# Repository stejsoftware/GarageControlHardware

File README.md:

# GarageControlHardwarae
Hardware design of Garage Controler

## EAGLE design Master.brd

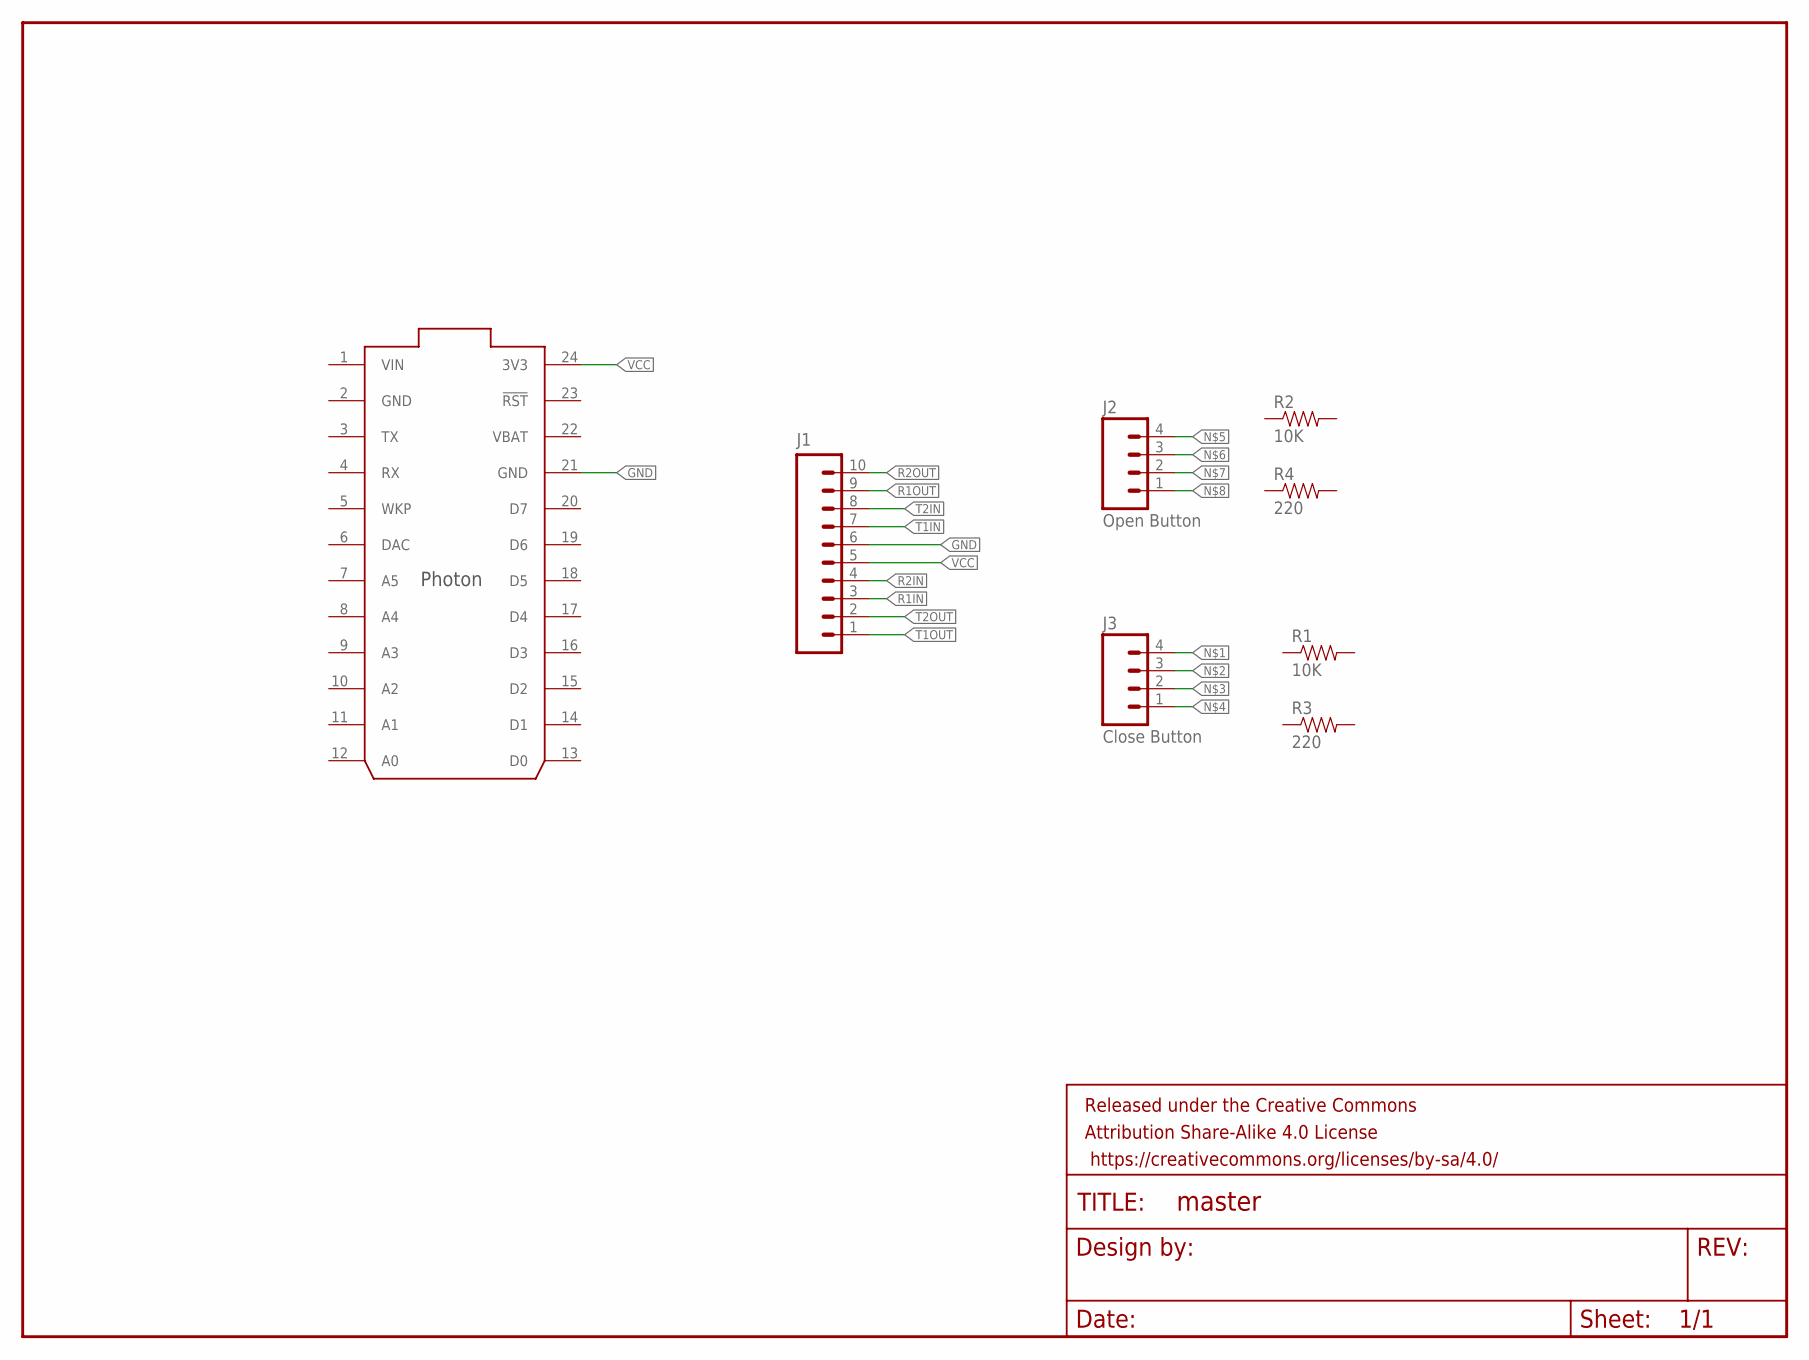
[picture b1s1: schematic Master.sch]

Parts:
FRAME1: FRAME-LETTERNO_PACKAGE; DUMMY
J1: M10SILK_FEMALE_PTH; 1X10
J2: Open Button; 1X04
J3: Close Button; 1X04
R1, R2: 10K; AXIAL-0.4
R3, R4: 220; AXIAL-0.4
U$1: PHOTON_WITH_HEADERS; PHOTON

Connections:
GND: J1.6, U$1.2 (GND), U$1.21 (GND)
R1IN: J1.3
R1OUT: J1.9
R2IN: J1.4
R2OUT: J1.10
T1IN: J1.7
T1OUT: J1.1
T2IN: J1.8
T2OUT: J1.2
VBAT: U$1.22 (VBAT)
VCC: J1.5, U$1.24 (3V3)
VIN: U$1.1 (VIN)

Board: 2 copper layers, 9 parts (0 on the bottom side), 2 nets, no tracks yet.

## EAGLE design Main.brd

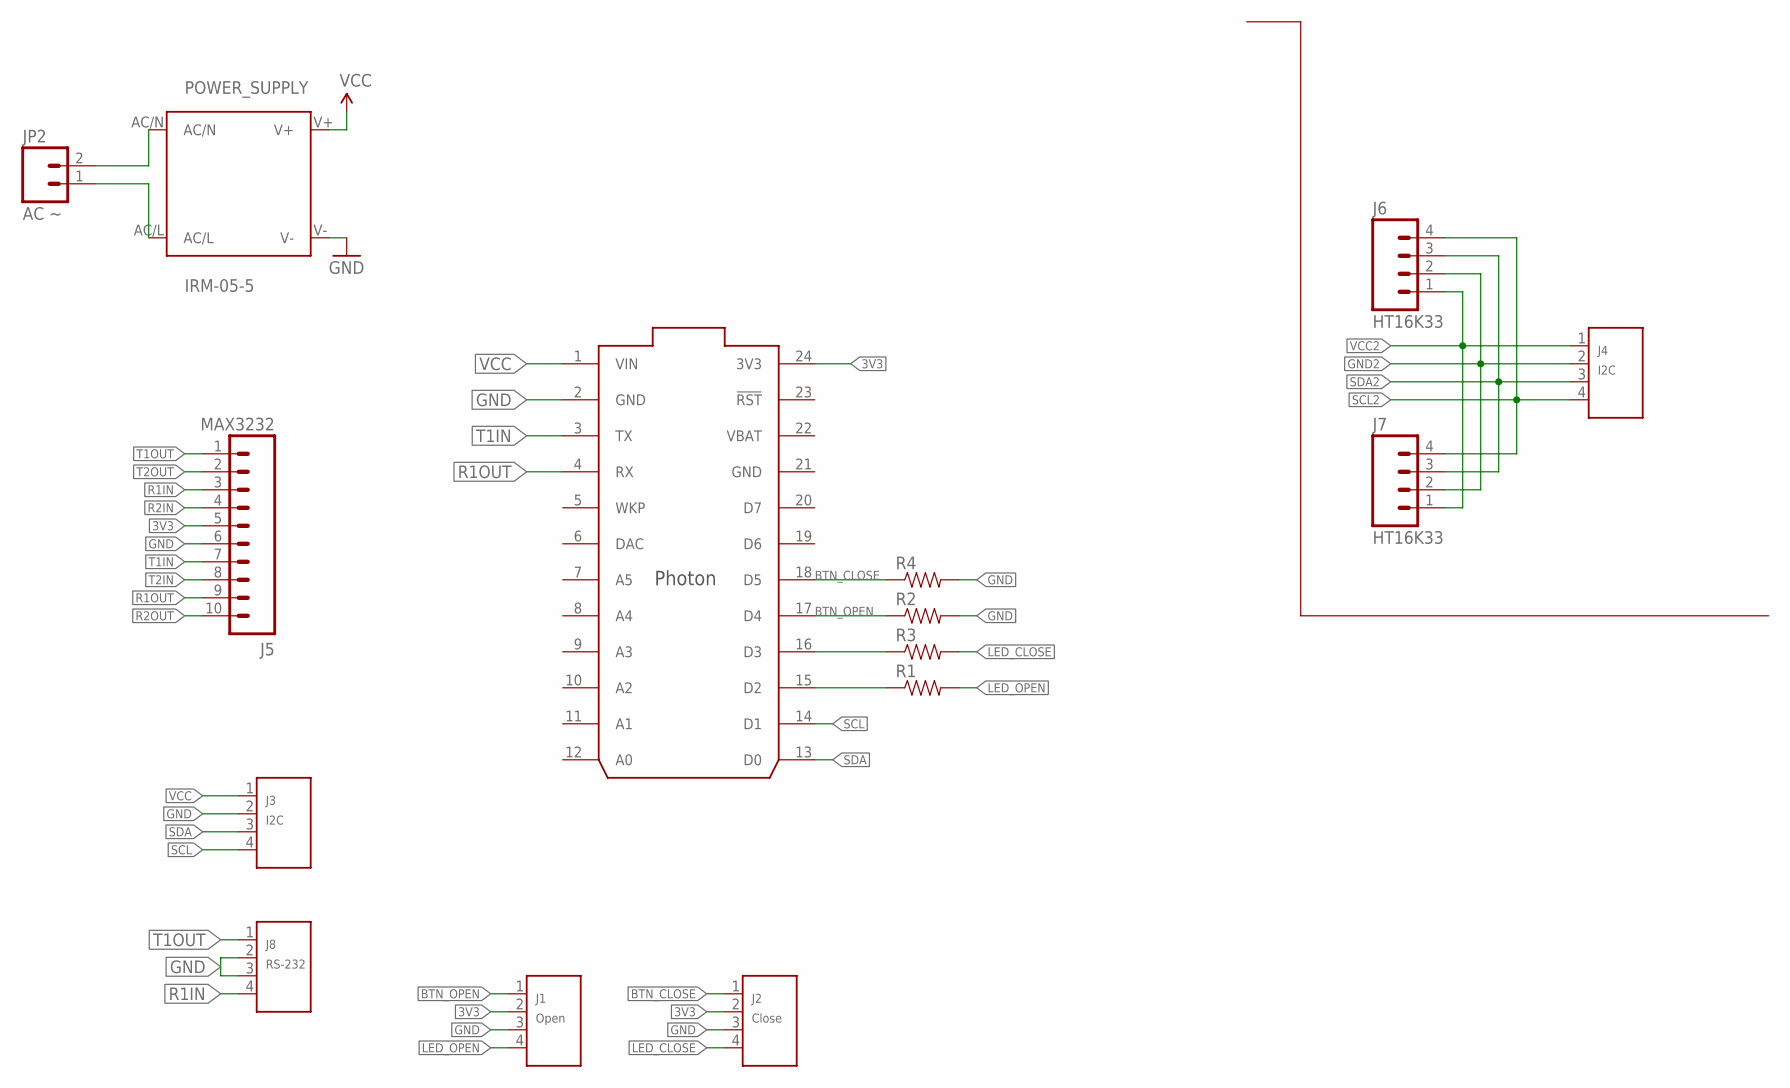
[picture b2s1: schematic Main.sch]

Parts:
J1: Open; HW4-2.0
J2: Close; HW4-2.0
J3, J4: I2C; HW4-2.0
J5: MAX3232; 1X10
J6, J7: HT16K33; 1X04
J8: RS-232; HW4-2.0
JP2: AC ~; SCREWTERMINAL-5MM-2
PHOTON: PHOTON
POWER_SUPPLY: IRM-05-5; IRM_05/10
R1, R2, R3, R4: RESISTORPTH-1/4W; AXIAL-0.4

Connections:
3V3: J1.2, J2.2, J5.5, PHOTON.24 (3V3)
BTN_CLOSE: J2.1, PHOTON.18 (D5), R4.P$1 (1)
BTN_OPEN: J1.1, PHOTON.17 (D4), R2.P$1 (1)
GND: J1.3, J2.3, J3.2, J5.6, J8.2, J8.3, PHOTON.2 (GND), PHOTON.21 (GND), POWER_SUPPLY.V-, R2.P$2 (2), R4.P$2 (2)
GND2: J4.2, J6.2, J7.2
LED_CLOSE: J2.4, R3.P$2 (2)
LED_OPEN: J1.4, R1.P$2 (2)
unnamed: JP2.1, POWER_SUPPLY.AC/L
unnamed: JP2.2, POWER_SUPPLY.AC/N
unnamed: PHOTON.16 (D3), R3.P$1 (1)
unnamed: PHOTON.15 (D2), R1.P$1 (1)
R1IN: J5.3, J8.4
R1OUT: J5.9, PHOTON.4 (RX)
R2IN: J5.4
R2OUT: J5.10
SCL: J3.4, PHOTON.14 (D1)
SCL2: J4.4, J6.4, J7.4
SDA: J3.3, PHOTON.13 (D0)
SDA2: J4.3, J6.3, J7.3
T1IN: J5.7, PHOTON.3 (TX)
T1OUT: J5.1, J8.1
T2IN: J5.8
T2OUT: J5.2
VBAT: PHOTON.22 (VBAT)
VCC: J3.1, PHOTON.1 (VIN), POWER_SUPPLY.V+
VCC2: J4.1, J6.1, J7.1

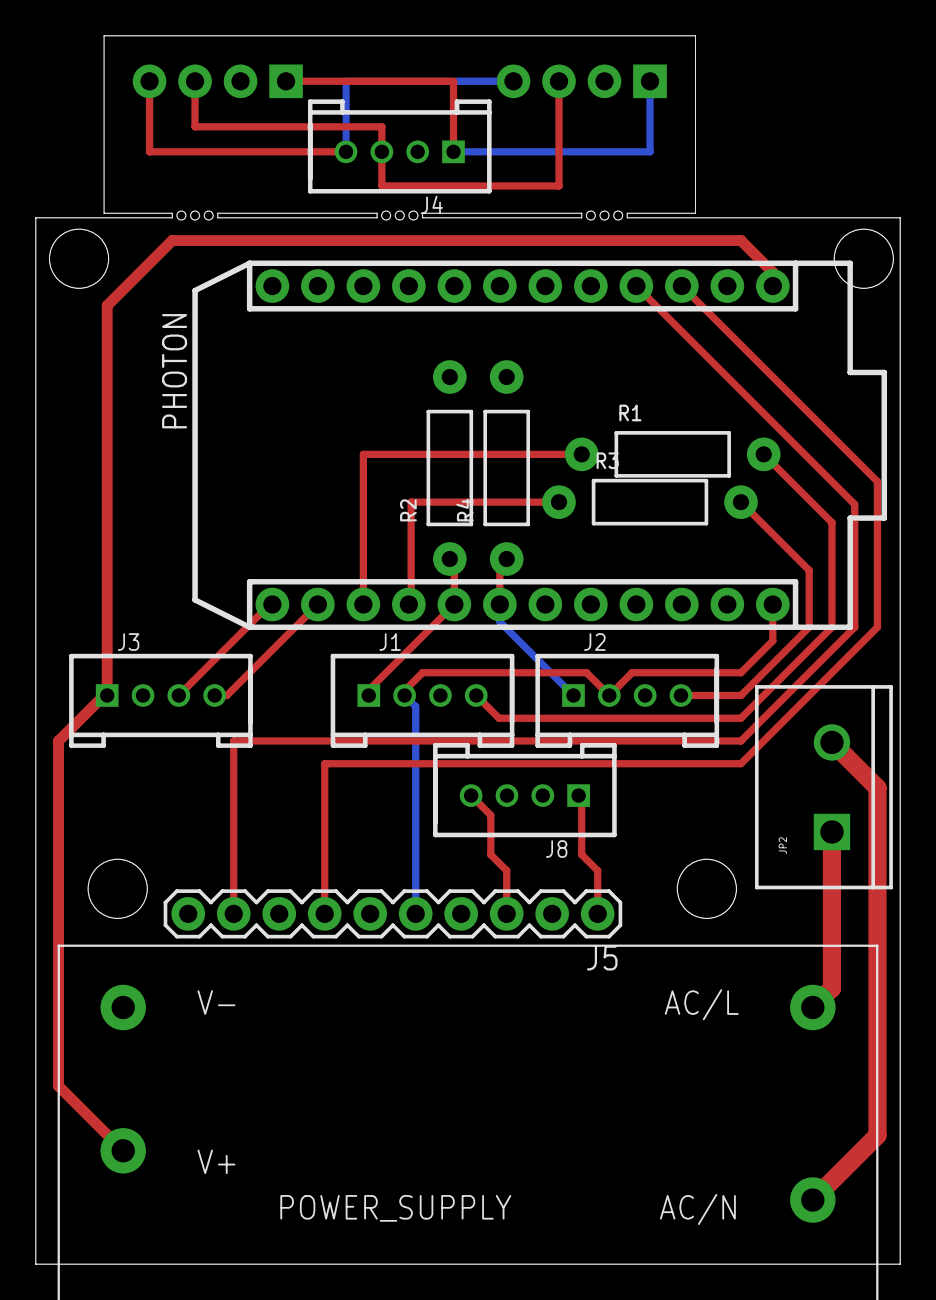
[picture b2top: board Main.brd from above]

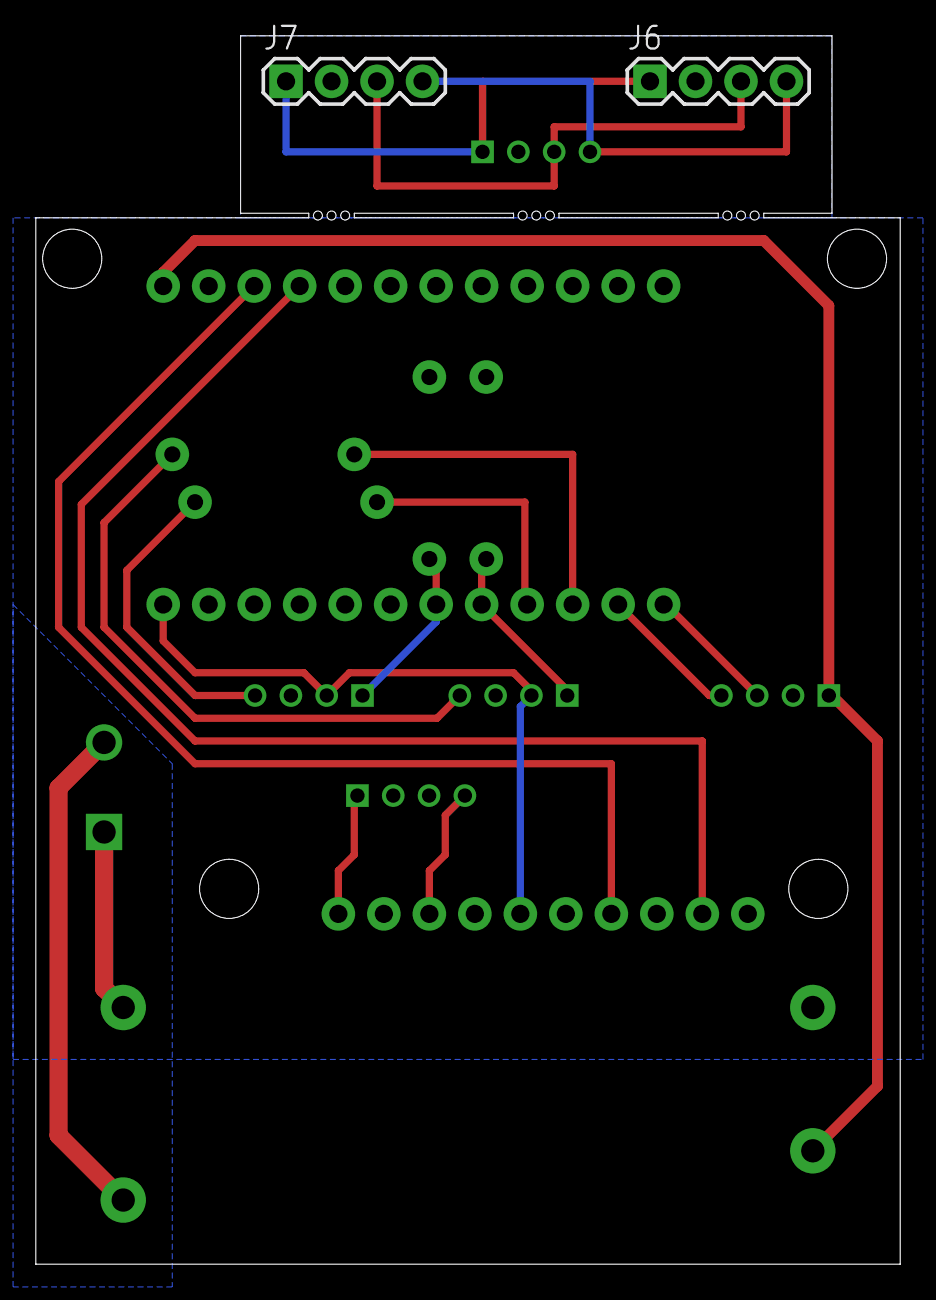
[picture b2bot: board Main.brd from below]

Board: 2 copper layers, 48.3 x 68.6 mm, 19 parts (2 on the bottom side), 21 nets.

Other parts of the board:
U$3, U$4, U$5, U$6: STAND-OFF

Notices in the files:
parts and their libraries:
SparkFun-Connectors: Licensing: Creative Commons ShareAlike 4.0 International - https://creativecommons.org/licenses/by-sa/4.0
SparkFun-Aesthetics: Released under the Creative Commons Attribution Share-Alike 4.0 License
SparkFun-Aesthetics: https://creativecommons.org/licenses/by-sa/4.0
